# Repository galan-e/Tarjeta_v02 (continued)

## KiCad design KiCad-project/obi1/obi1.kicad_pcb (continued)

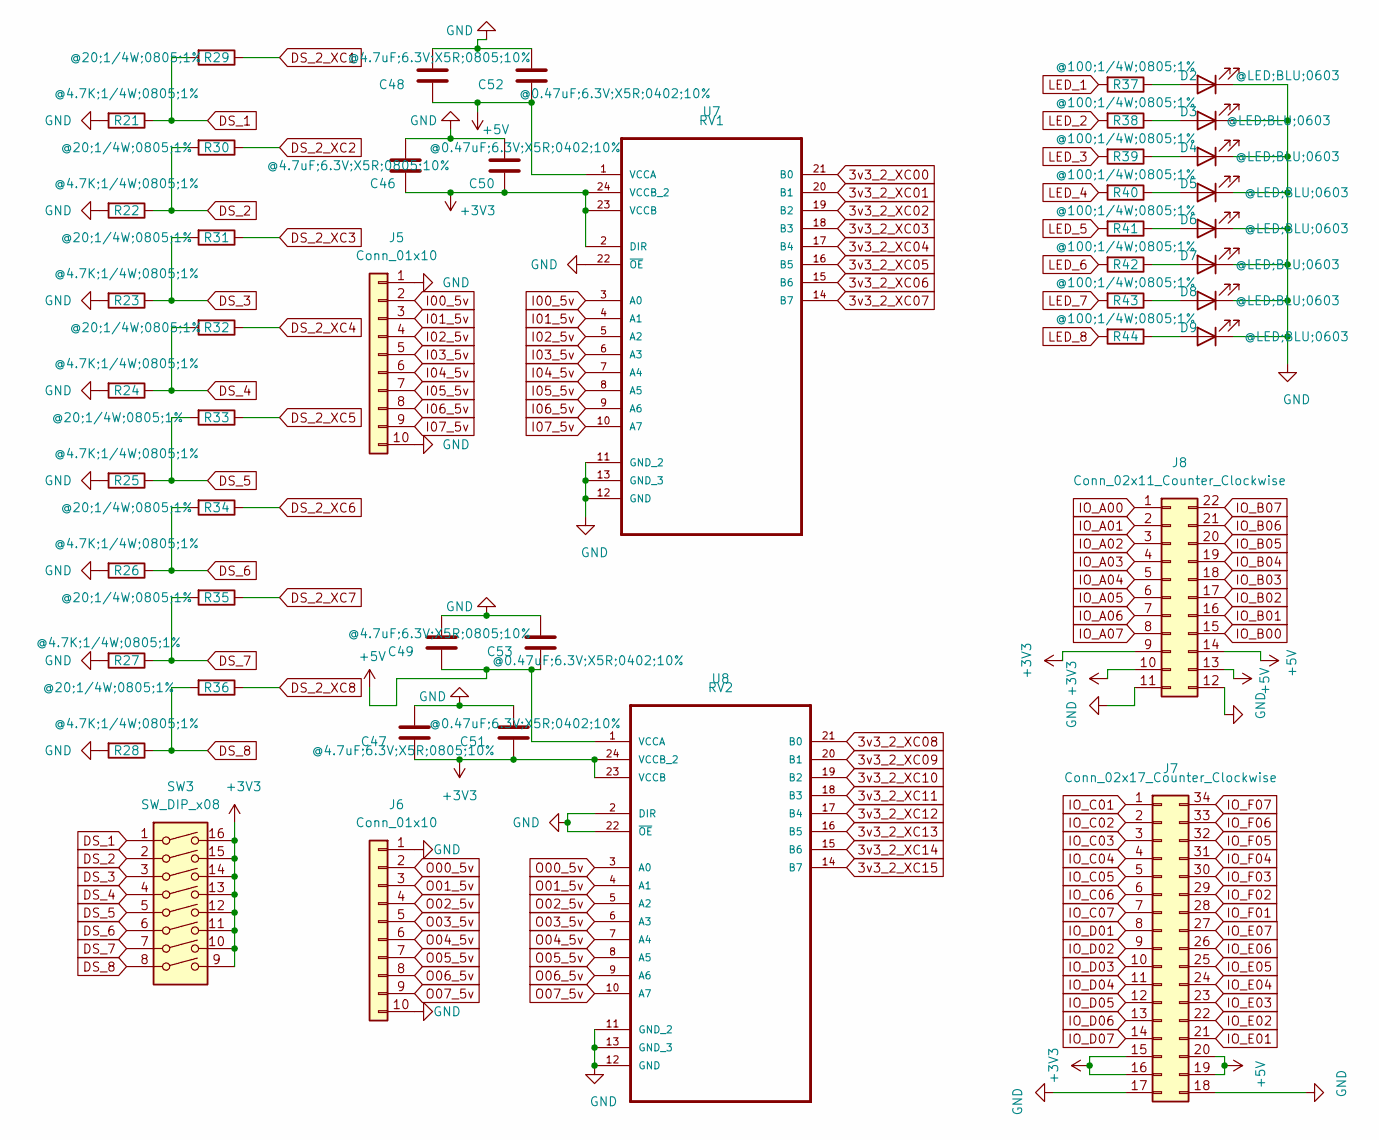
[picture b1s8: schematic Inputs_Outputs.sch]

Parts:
C46, C47, C48, C49: @4.7uF;6.3V;X5R;0805;10%; C_0805_2012Metric_Pad1.18x1.45mm_HandSolder
C50, C51, C52, C53: @0.47uF;6.3V;X5R;0402;10%; C_0402_1005Metric_Pad0.74x0.62mm_HandSolder
D2, D3, D4, D5, D6, D7, D8, D9: @LED;BLU;0603; LED_0603_1608Metric_Pad1.05x0.95mm_HandSolder
J5, J6: Conn_01x10; PinSocket_1x10_P2.54mm_Vertical
J7: Conn_02x17_Counter_Clockwise; PinSocket_2x17_P2.54mm_Vertical
J8: Conn_02x11_Counter_Clockwise; PinSocket_2x11_P2.54mm_Vertical
R21, R22, R23, R24, R25, R26, R27, R28: @4.7K;1/4W;0805;1%; R_0805_2012Metric_Pad1.20x1.40mm_HandSolder
R29, R30, R31, R32, R33, R34, R35, R36: @20;1/4W;0805;1%; R_0805_2012Metric_Pad1.20x1.40mm_HandSolder
R37, R38, R39, R40, R41, R42, R43, R44: @100;1/4W;0805;1%; R_0805_2012Metric_Pad1.20x1.40mm_HandSolder
SW3: SW_DIP_x08; SW_DIP_SPSTx08_Slide_9.78x22.5mm_W7.62mm_P2.54mm
U7: RV1; SOP65P640X110-24N
U8: RV2; SOP65P640X110-24N

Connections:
3v3_2_XC00: U7.21 (B0); also elsewhere on the board
3v3_2_XC01: U7.20 (B1); also elsewhere on the board
3v3_2_XC02: U7.19 (B2); also elsewhere on the board
3v3_2_XC03: U7.18 (B3); also elsewhere on the board
3v3_2_XC04: U7.17 (B4); also elsewhere on the board
3v3_2_XC05: U7.16 (B5); also elsewhere on the board
3v3_2_XC06: U7.15 (B6); also elsewhere on the board
3v3_2_XC07: U7.14 (B7); also elsewhere on the board
3v3_2_XC08: U8.21 (B0); also elsewhere on the board
3v3_2_XC09: U8.20 (B1); also elsewhere on the board
3v3_2_XC10: U8.19 (B2); also elsewhere on the board
3v3_2_XC11: U8.18 (B3); also elsewhere on the board
3v3_2_XC12: U8.17 (B4); also elsewhere on the board
3v3_2_XC13: U8.16 (B5); also elsewhere on the board
3v3_2_XC14: U8.15 (B6); also elsewhere on the board
3v3_2_XC15: U8.14 (B7); also elsewhere on the board
+3V3: C46.1, C47.1, C50.1, C51.1, J7.15, J7.16, J8.9, J8.10, SW3.9, SW3.10, SW3.11, SW3.12, SW3.13, SW3.14, SW3.15, SW3.16, U7.2 (DIR), U7.23 (VCCB), U7.24 (VCCB_2), U8.23 (VCCB), U8.24 (VCCB_2); also elsewhere on the board
+5V: C48.1, C49.1, C52.1, C53.1, J7.19, J7.20, J8.13, J8.14, U7.1 (VCCA), U8.1 (VCCA); also elsewhere on the board
DS_1: R21.1, R29.2, SW3.1
DS_2: R22.1, R30.2, SW3.2
DS_2_XC1: R29.1; also elsewhere on the board
DS_2_XC2: R30.1; also elsewhere on the board
DS_2_XC3: R31.1; also elsewhere on the board
DS_2_XC4: R32.1; also elsewhere on the board
DS_2_XC5: R33.1; also elsewhere on the board
DS_2_XC6: R34.1; also elsewhere on the board
DS_2_XC7: R35.1; also elsewhere on the board
DS_2_XC8: R36.1; also elsewhere on the board
DS_3: R23.1, R31.2, SW3.3
DS_4: R24.1, R32.2, SW3.4
DS_5: R25.1, R33.2, SW3.5
DS_6: R26.1, R34.2, SW3.6
DS_7: R27.1, R35.2, SW3.7
DS_8: R28.1, R36.2, SW3.8
GND: C46.2, C47.2, C48.2, C49.2, C50.2, C51.2, C52.2, C53.2, D2.1 (K), D3.1 (K), D4.1 (K), D5.1 (K), D6.1 (K), D7.1 (K), D8.1 (K), D9.1 (K), J5.1, J5.10, J6.1, J6.10, J7.17, J7.18, J8.11, J8.12, R21.2, R22.2, R23.2, R24.2, R25.2, R26.2, R27.2, R28.2, U7.11 (GND_2), U7.12 (GND), U7.13 (GND_3), U7.22 (~OE), U8.2 (DIR), U8.11 (GND_2), U8.12 (GND), U8.13 (GND_3), U8.22 (~OE); also elsewhere on the board
I00_5v: J5.2, U7.3 (A0)
I01_5v: J5.3, U7.4 (A1)
I02_5v: J5.4, U7.5 (A2)
I03_5v: J5.5, U7.6 (A3)
I04_5v: J5.6, U7.7 (A4)
I05_5v: J5.7, U7.8 (A5)
I06_5v: J5.8, U7.9 (A6)
I07_5v: J5.9, U7.10 (A7)
IO_A00: J8.1; also elsewhere on the board
IO_A01: J8.2; also elsewhere on the board
IO_A02: J8.3; also elsewhere on the board
IO_A03: J8.4; also elsewhere on the board
IO_A04: J8.5; also elsewhere on the board
IO_A05: J8.6; also elsewhere on the board
IO_A06: J8.7; also elsewhere on the board
IO_A07: J8.8; also elsewhere on the board
IO_B00: J8.15; also elsewhere on the board
IO_B01: J8.16; also elsewhere on the board
IO_B02: J8.17; also elsewhere on the board
IO_B03: J8.18; also elsewhere on the board
IO_B04: J8.19; also elsewhere on the board
IO_B05: J8.20; also elsewhere on the board
IO_B06: J8.21; also elsewhere on the board
IO_B07: J8.22; also elsewhere on the board
IO_C01: J7.1; also elsewhere on the board
IO_C02: J7.2; also elsewhere on the board
IO_C03: J7.3; also elsewhere on the board
IO_C04: J7.4; also elsewhere on the board
IO_C05: J7.5; also elsewhere on the board
IO_C06: J7.6; also elsewhere on the board
IO_C07: J7.7; also elsewhere on the board
IO_D01: J7.8; also elsewhere on the board
IO_D02: J7.9; also elsewhere on the board
IO_D03: J7.10; also elsewhere on the board
IO_D04: J7.11; also elsewhere on the board
IO_D05: J7.12; also elsewhere on the board
IO_D06: J7.13; also elsewhere on the board
IO_D07: J7.14; also elsewhere on the board
IO_E01: J7.21; also elsewhere on the board
IO_E02: J7.22; also elsewhere on the board
IO_E03: J7.23; also elsewhere on the board
IO_E04: J7.24; also elsewhere on the board
IO_E05: J7.25; also elsewhere on the board
IO_E06: J7.26; also elsewhere on the board
IO_E07: J7.27; also elsewhere on the board
IO_F01: J7.28; also elsewhere on the board
IO_F02: J7.29; also elsewhere on the board
IO_F03: J7.30; also elsewhere on the board
IO_F04: J7.31; also elsewhere on the board
IO_F05: J7.32; also elsewhere on the board
IO_F06: J7.33; also elsewhere on the board
IO_F07: J7.34; also elsewhere on the board
LED_1: R37.2; also elsewhere on the board
LED_2: R38.2; also elsewhere on the board
LED_3: R39.2; also elsewhere on the board
LED_4: R40.2; also elsewhere on the board
LED_5: R41.2; also elsewhere on the board
LED_6: R42.2; also elsewhere on the board
LED_7: R43.2; also elsewhere on the board
LED_8: R44.2; also elsewhere on the board
unnamed: D2.2 (A), R37.1
unnamed: D3.2 (A), R38.1
unnamed: D4.2 (A), R39.1
unnamed: D5.2 (A), R40.1
unnamed: D6.2 (A), R41.1
unnamed: D7.2 (A), R42.1
unnamed: D8.2 (A), R43.1
unnamed: D9.2 (A), R44.1
O00_5v: J6.2, U8.3 (A0)
O01_5v: J6.3, U8.4 (A1)
O02_5v: J6.4, U8.5 (A2)
O03_5v: J6.5, U8.6 (A3)
O04_5v: J6.6, U8.7 (A4)
O05_5v: J6.7, U8.8 (A5)
O06_5v: J6.8, U8.9 (A6)
O07_5v: J6.9, U8.10 (A7)

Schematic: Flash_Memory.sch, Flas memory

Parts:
C54: @0.47uF;6.3V;X5R;0402;10%; C_0402_1005Metric_Pad0.74x0.62mm_HandSolder
C55: @4.7uF;6.3V;X5R;0805;10%; C_0805_2012Metric_Pad1.18x1.45mm_HandSolder
IC3: FLASH; SOIC127P800X216-8N; Manufacturer_Part_Number S25FL064LABMFI013; Mouser Part Number 727-S25FL064LAMFI013
R45, R46, R48, R49: @100;1/4W;0805;1%; R_0805_2012Metric_Pad1.20x1.40mm_HandSolder
R47: @2.4K;1/4W;0805;1%; R_0805_2012Metric_Pad1.20x1.40mm_HandSolder

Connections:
+3V3: C54.2, C55.2, IC3.8 (VCC), R47.1; also elsewhere on the board
GND: C54.1, C55.1, IC3.4 (VSS); also elsewhere on the board
unnamed: IC3.2 (SO/IO1), R46.1
unnamed: IC3.3 (WP#/IO2), R45.1
unnamed: IC3.5 (SI/IO0), R49.2
unnamed: IC3.7 (IO3/RESET#), R48.2
XC_N12: R45.2; also elsewhere on the board
XC_P10: R46.2; also elsewhere on the board
XC_P12: R48.1; also elsewhere on the board
XC_R11: IC3.6 (SCK); also elsewhere on the board
XC_T3: IC3.1 (CS#), R47.2; also elsewhere on the board
XC_T10: R49.1; also elsewhere on the board

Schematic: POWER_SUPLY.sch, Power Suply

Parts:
C1: @4.7uF;6.3V;X5R;0805;10%; C_0805_2012Metric_Pad1.18x1.45mm_HandSolder
C2, C3, C4, C5: @1uF;6.3V;X5R;0805;10%; C_0805_2012Metric_Pad1.18x1.45mm_HandSolder
J1: USB; 101181930001LF
R1: @1M;1/2W;0805;1%; R_0805_2012Metric_Pad1.20x1.40mm_HandSolder
U1: RG3V3; SOT230P700X180-4N3.3
U2: REG1V2; SOT230P700X180-4N1.2

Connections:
+1V2: C5.1, U2.2 (OUT), U2.4 (VOUT); also elsewhere on the board
+3V3: C4.1, U1.2 (OUT), U1.4 (VOUT); also elsewhere on the board
+5V: C2.1, C3.1, J1.1, J1.4, U1.3 (IN), U2.3 (IN); also elsewhere on the board
D+: J1.3; also elsewhere on the board
D-: J1.2; also elsewhere on the board
GND: C1.2, C2.2, C3.2, C4.2, C5.2, J1.5, R1.2, U1.1 (ADJ/GND), U2.1 (ADJ/GND); also elsewhere on the board
unnamed: C1.1, J1.MH1, J1.MH2, J1.MP1, J1.MP2, J1.MP3, J1.MP4, R1.1

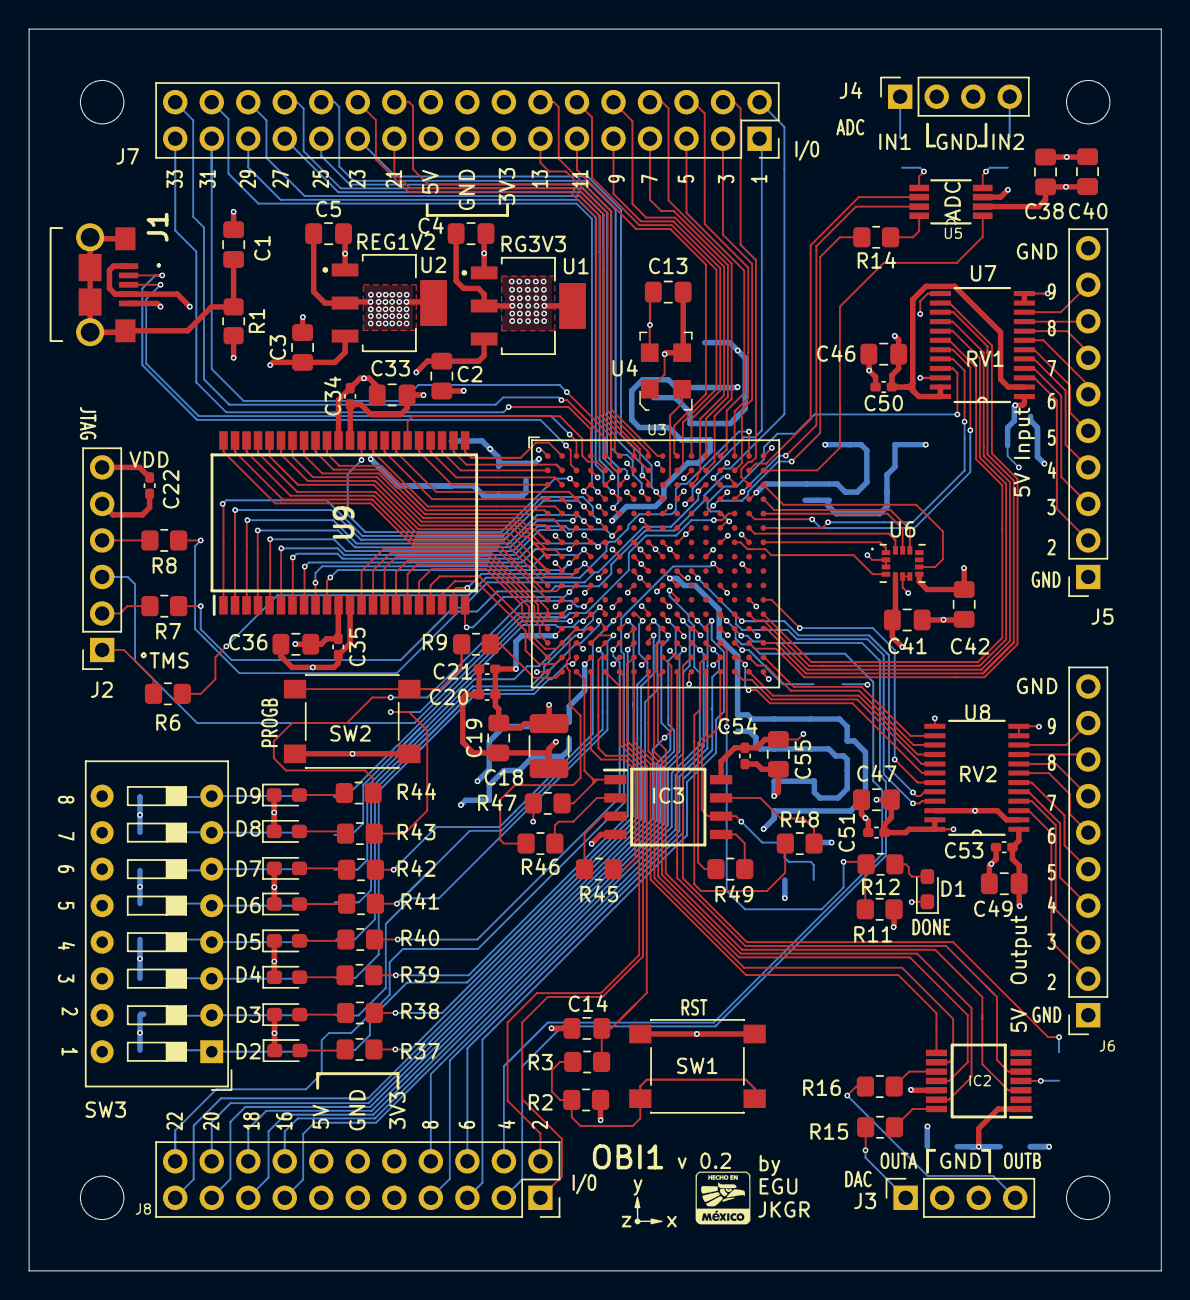
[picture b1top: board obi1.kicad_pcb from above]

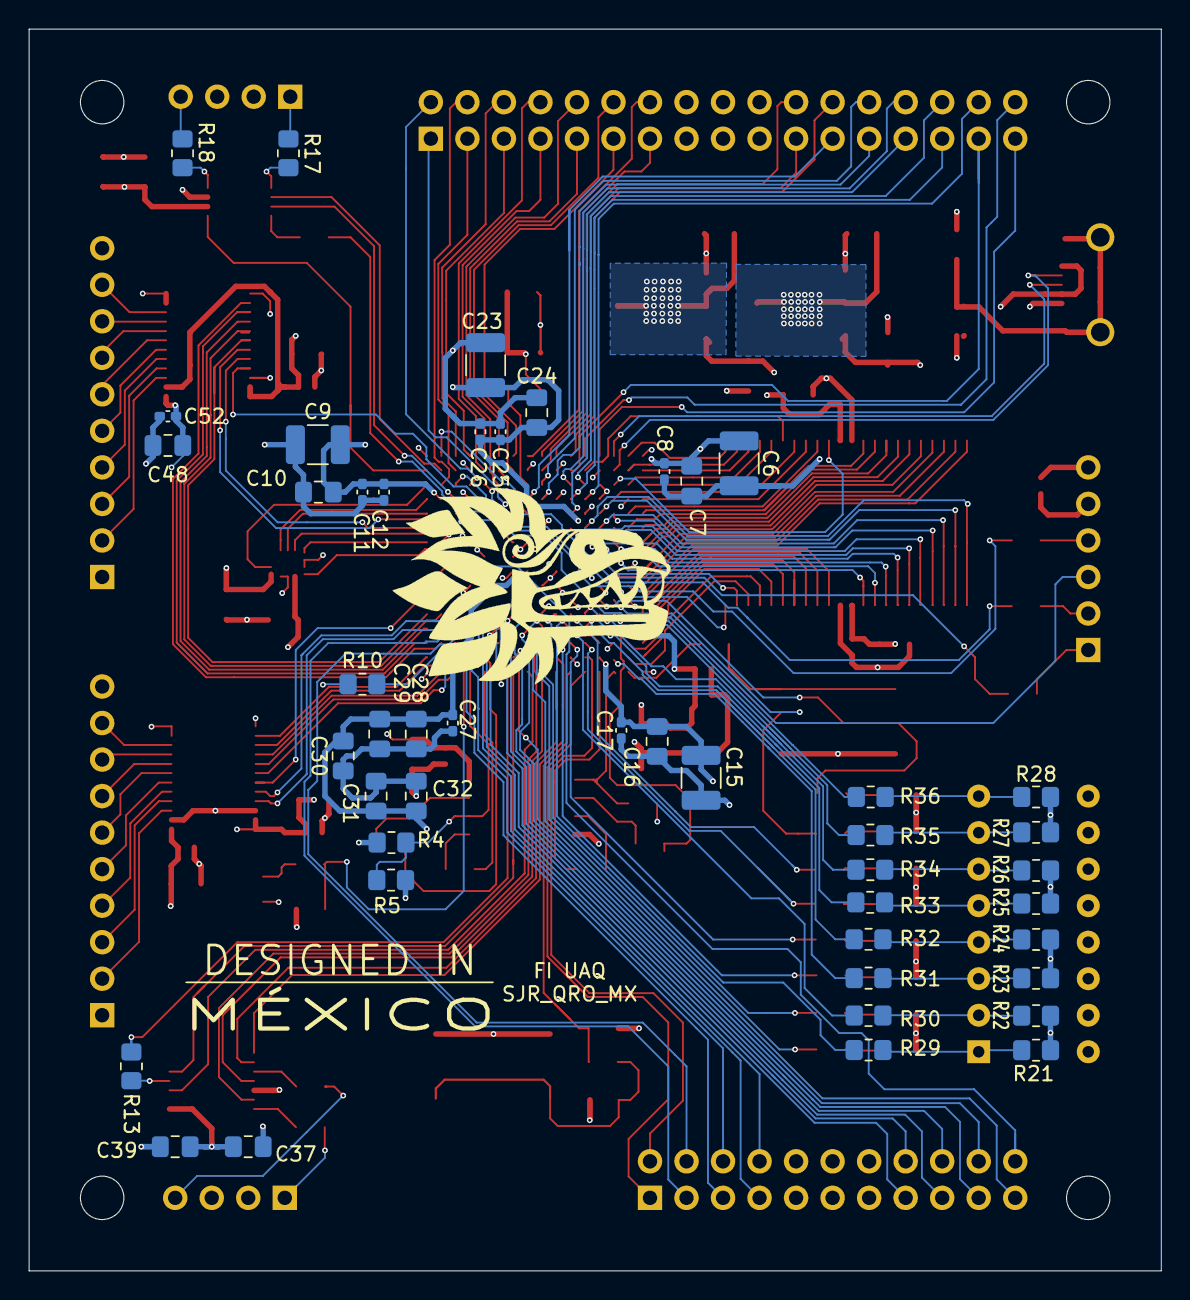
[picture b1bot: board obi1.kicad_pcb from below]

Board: 4 copper layers, 78.7 x 86.4 mm, 130 parts (46 on the bottom side), 207 nets.

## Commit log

2021-03-30 Update PCB imu
2021-03-30 Routear
2021-04-08 Resize board, change layout, re-route IO pins, new imu added
2021-04-08 Text in Silk layer adjusted
2021-04-09 Changed RAM by Cypres Model -rebuild symbolic and changed footprint
2021-04-09 BOM in proceso
2021-04-15 Gerbers Files generated and BOM already done
2021-04-30 IMU changed again, Final IMU= LSM6DSMTR, First Order to OSHPark
